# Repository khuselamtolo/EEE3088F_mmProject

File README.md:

# EEE3088F_mmProject
## PCB Designs of a power subsystem, intended for a micro-mouse maze-solving robot
This repository is for Group 64's design files for the Micro-mouse Power Subsystem Project, as required by the EEE3088F course from the University of Cape Town.

We, as the students, give our consent for third parties to use, modify, distribute and sell the files found within in repository, but please contact the University of Cape Town for full legal licensing.

Group 64's Student Numbers: MTLKHU009, VRSNEO001

## Repository File Layout
In the main directory of the repository (where this README.md file is) is the main files of the project (.kicad_pro .kicad_sch and .kicad_pcb).
The folder 'jlcpcb' contains the production files, formatted for the manufacturer JLCPCB.
The folders 'Connector_USB.lib' and 'Connector_USB.pretty' contain footprint files for USB connectors, for either Windows or MacOS (respectively). These files are referenced for the USB-C connector in the project.

## How to use
Download the repository, and open the file 'EEE3088F_micro_mouse_power_subsystem.kicad_pro' using Ki_CAD 9.0 or any later version that's compatible with KiCAD 9.0 files.

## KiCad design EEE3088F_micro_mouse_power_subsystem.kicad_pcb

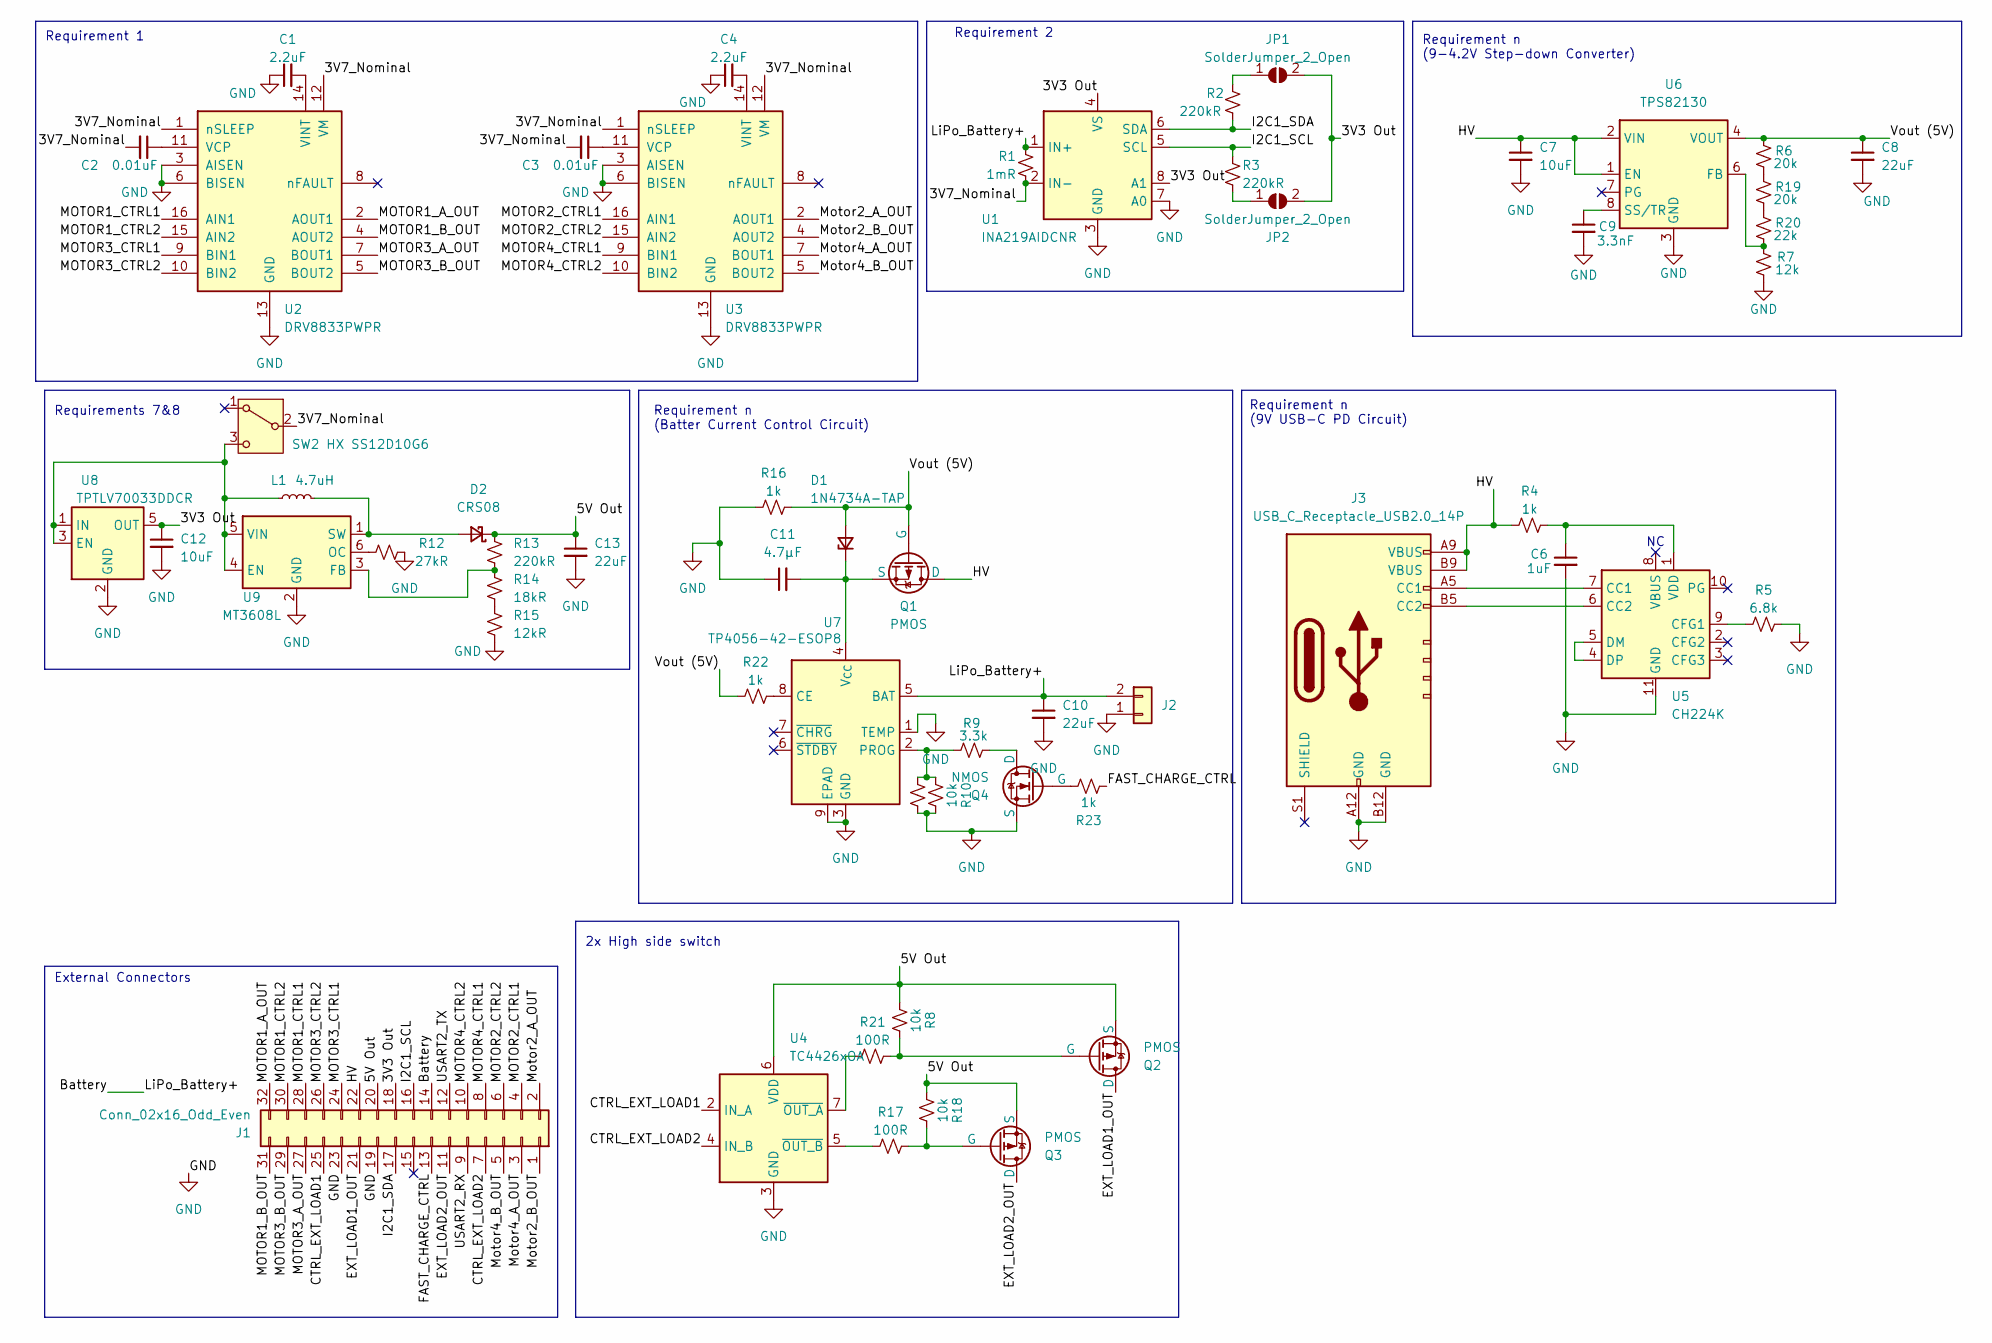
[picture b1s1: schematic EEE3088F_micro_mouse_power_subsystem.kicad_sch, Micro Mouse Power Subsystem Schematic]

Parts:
C1, C4: 2.2uF; C_0402_1005Metric; LCSC C12530
C2, C3: 0.01uF; C_0402_1005Metric; LCSC C15195
C6: 1uF; C_0402_1005Metric; LCSC C1848
C7, C12: 10uF; C_0402_1005Metric; LCSC C15525
C8, C10, C13: 22uF; C_0603_1608Metric; LCSC C59461
C9: 3.3nF; C_0603_1608Metric; LCSC C1613
C11: 4.7µF; C_0805_2012Metric; LCSC C1779
D1: 1N4734A-TAP; D_DO-35_SOD27_P2.54mm_Vertical_AnodeUp; LCSC C241984
D2: CRS08; D_1206_3216Metric; LCSC C475662
J1: Conn_02x16_Odd_Even; PinHeader_2x16_P2.54mm_Vertical
J2: Conn_01x02; JST_PH_S2B-PH-K_1x02_P2.00mm_Horizontal
J3: USB_C_Receptacle_USB2.0_14P; USB_C_Receptacle_GCT_USB4125-xx-x-0190_6P_TopMnt_Horizontal; LCSC C168701
JP1, JP2: SolderJumper_2_Open; SolderJumper-2_P1.3mm_Open_TrianglePad1.0x1.5mm
L1: 4.7uH; L_1008_2520Metric; LCSC C5832360
Q1, Q2, Q3: PMOS; SOT-23; LCSC C5224173
Q4: NMOS; SOT-23; LCSC C8545
R1: 1mR; R_1206_3216Metric; LCSC C7419993
R2, R3, R13: 220kR; R_0603_1608Metric; LCSC C22961
R4, R16, R22, R23: 1k; R_1206_3216Metric; LCSC C4410
R5: 6.8k; R_0805_2012Metric; LCSC C17772
R6, R19: 20k; R_0603_1608Metric; LCSC C4184
R7: 12k; R_0402_1005Metric; LCSC C25752
R8, R10, R11, R18: 10k; R_0603_1608Metric; LCSC C25804
R9: 3.3k; R_0603_1608Metric; LCSC C22978
R12: 27kR; R_0603_1608Metric; LCSC C22967
R14: 18kR; R_0603_1608Metric; LCSC C25810
R15: 12kR; R_0402_1005Metric; LCSC C25752
R17, R21: 100R; R_0805_2012Metric; LCSC C17408
R20: 22k; R_0603_1608Metric; LCSC C31850
SW2: HX SS12D10G6; SolderWire-0.75sqmm_1x03_P4.8mm_D1.25mm_OD2.3mm; LCSC C19189121
U1: INA219AIDCNR; SOT-23-8; LCSC C87469
U2, U3: DRV8833PWPR; TSSOP-16_4.4x5mm_P0.65mm; LCSC C50506
U4: TC4426xOA; SOIC-8_3.9x4.9mm_P1.27mm
U5: CH224K; SSOP-10-1EP_3.9x4.9mm_P1mm_EP2.1x3.3mm; LCSC C970725
U6: TPS82130; Texas_SIL0008D_MicroSiP-8-1EP_2.8x3mm_P0.65mm_EP1.1x1.9mm_T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; LCSC C473914
U7: TP4056-42-ESOP8; SOIC-8-1EP_3.9x4.9mm_P1.27mm_EP2.41x3.3mm_ThermalVias; LCSC C21417
U8: TPTLV70033DDCR; SOT-23-5; LCSC C2937039
U9: MT3608L; SOT-23-6; LCSC C2932326

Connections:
/3V3 Out: C12.1, J1.18, JP1.2 (B), JP2.2 (B), U1.4 (VS), U1.8 (A1), U8.5 (OUT)
/3V7_Nominal: C2.2, C3.2, R1.2, SW2.2 (B), U1.2 (IN-), U2.1 (nSLEEP), U2.12 (VM), U3.1 (nSLEEP), U3.12 (VM)
/5V Out: C13.1, D2.1 (K), J1.20, Q2.3 (S), Q3.3 (S), R8.1, R13.1, R18.1, U4.6 (VDD)
/Battery: C10.1, J1.14, J2.2 (Pin_1), R1.1, U1.1 (IN+), U7.5 (BAT)
/CTRL_EXT_LOAD1: J1.25, U4.2 (IN_A)
/CTRL_EXT_LOAD2: J1.7, U4.4 (IN_B)
/EXT_LOAD1_OUT: J1.21, Q2.1 (D)
/EXT_LOAD2_OUT: J1.11, Q3.1 (D)
/FAST_CHARGE_CTRL: J1.13, R23.2
/HV: C7.1, J1.22, J3.A9 (VBUS), J3.B4 (VBUS), J3.B9 (VBUS), Q1.1 (D), R4.2, U6.1 (EN), U6.2 (VIN)
/I2C1_SCL: J1.16, R3.1, U1.5 (SCL)
/I2C1_SDA: J1.17, R2.2, U1.6 (SDA)
/MOTOR1_A_OUT: J1.32, U2.2 (AOUT1)
/MOTOR1_B_OUT: J1.31, U2.4 (AOUT2)
/MOTOR1_CTRL1: J1.28, U2.16 (AIN1)
/MOTOR1_CTRL2: J1.30, U2.15 (AIN2)
/MOTOR2_CTRL1: J1.4, U3.16 (AIN1)
/MOTOR2_CTRL2: J1.6, U3.15 (AIN2)
/MOTOR3_A_OUT: J1.27, U2.7 (BOUT1)
/MOTOR3_B_OUT: J1.29, U2.5 (BOUT2)
/MOTOR3_CTRL1: J1.24, U2.9 (BIN1)
/MOTOR3_CTRL2: J1.26, U2.10 (BIN2)
/MOTOR4_CTRL1: J1.8, U3.9 (BIN1)
/MOTOR4_CTRL2: J1.10, U3.10 (BIN2)
/Motor2_A_OUT: J1.2, U3.2 (AOUT1)
/Motor2_B_OUT: J1.1, U3.4 (AOUT2)
/Motor4_A_OUT: J1.3, U3.7 (BOUT1)
/Motor4_B_OUT: J1.5, U3.5 (BOUT2)
/USART2_RX: J1.9
/USART2_TX: J1.12
/Vout (5V): C8.1, D1.2 (A), Q1.2 (G), R6.1, R16.1, R22.2, U6.4 (VOUT), U6.5 (VOUT)
GND: C1.1, C4.1, C6.2, C7.2, C8.2, C9.2, C10.2, C11.1, C12.2, C13.2, J1.19, J1.23, J2.1 (Pin_2), J3.A12 (GND), J3.B1 (GND), J3.B12 (GND), Q4.3 (S), R5.2, R7.2, R10.2, R11.2, R12.2, R15.2, R16.2, U1.3 (GND), U1.7 (A0), U2.3 (AISEN), U2.6 (BISEN), U2.13 (GND), U3.3 (AISEN), U3.6 (BISEN), U3.13 (GND), U4.3 (GND), U5.11 (GND), U6.3 (GND), U6.9 (GND), U7.1 (TEMP), U7.3 (GND), U7.9 (EPAD), U8.2 (GND), U8.4 (GND), U9.2 (GND)
unnamed: C11.2, D1.1 (K), Q1.3 (S), U7.4 (V_{CC})
unnamed: D2.2 (A), L1.2, U9.1 (SW)
unnamed: J3.A5 (CC1), U5.7 (CC1)
unnamed: J3.B5 (CC2), U5.6 (CC2)
unnamed: JP1.1 (A), R2.1
unnamed: JP2.1 (A), R3.2
unnamed: Q2.2 (G), R8.2, R21.2
unnamed: Q3.2 (G), R17.2, R18.2
unnamed: Q4.1 (D), R9.2
unnamed: Q4.2 (G), R23.1
unnamed: R14.2, R15.1
unnamed: R6.2, R19.1
unnamed: R19.2, R20.1
unnamed: L1.1, SW2.3 (C), U8.1 (IN), U8.3 (EN), U9.4 (EN), U9.5 (VIN)
unnamed: C2.1, U2.11 (VCP)
unnamed: C1.2, U2.14 (VINT)
unnamed: C3.1, U3.11 (VCP)
unnamed: C4.2, U3.14 (VINT)
unnamed: R21.1, U4.7 (~OUT_A)
unnamed: R17.1, U4.5 (~OUT_B)
unnamed: R5.1, U5.9 (CFG1)
unnamed: U5.4 (DP), U5.5 (DM)
unnamed: C6.1, R4.1, U5.1 (VDD)
unnamed: R7.1, R20.2, U6.6 (FB)
unnamed: C9.1, U6.8 (SS/TR)
unnamed: R22.1, U7.8 (CE)
unnamed: R9.1, R10.1, R11.1, U7.2 (PROG)
unnamed: R13.2, R14.1, U9.3 (FB)
unnamed: R12.1, U9.6 (OC)

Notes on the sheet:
Requirement n (9-4.2V Step-down Converter)
Requirement n (9V USB-C PD Circuit)
2x High side switch
Requirement 1
Requirement n (Batter Current Control Circuit)
Requirements 7&8
External Connectors
Requirement 2

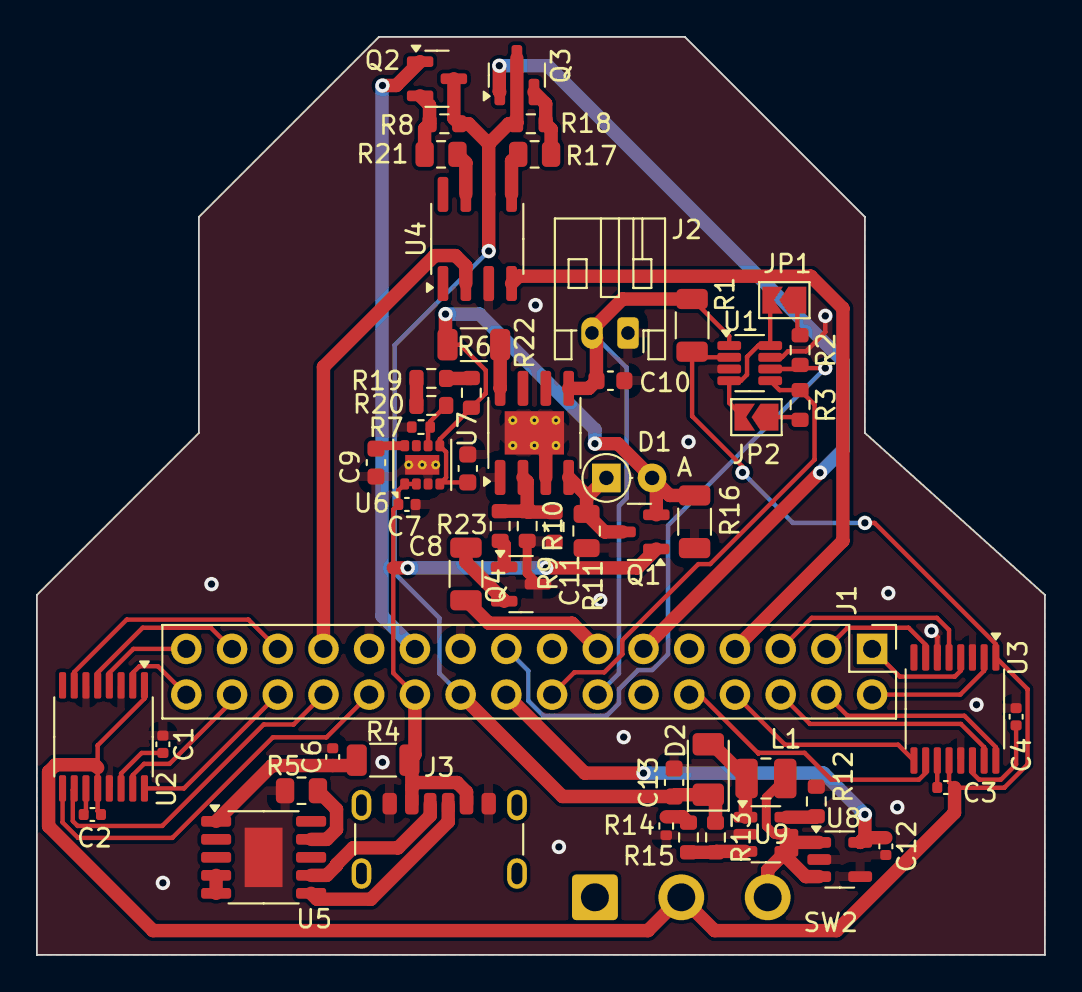
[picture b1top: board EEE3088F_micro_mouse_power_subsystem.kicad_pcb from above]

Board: 2 copper layers, 56.0 x 51.0 mm, 57 parts (0 on the bottom side), 59 nets.

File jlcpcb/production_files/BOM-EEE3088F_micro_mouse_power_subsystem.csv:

Comment,Designator,Footprint,LCSC,Quantity
2.2uF,"C1,C4",C_0402_1005Metric,C12530,2
TC4426xOA,U4,SOIC-8_3.9x4.9mm_P1.27mm,C148047,1
0.01uF,"C2,C3",C_0402_1005Metric,C15195,2
10uF,"C12,C7",C_0402_1005Metric,C15525,2
3.3nF,C9,C_0603_1608Metric,C1613,1
100R,"R17,R21",R_0805_2012Metric,C17408,2
6.8k,R5,R_0805_2012Metric,C17772,1
4.7µF,C11,C_0805_2012Metric,C1779,1
1uF,C6,C_0402_1005Metric,C1848,1
HX SS12D10G6,SW2,SolderWire-0.75sqmm_1x03_P4.8mm_D1.25mm_OD2.3mm,C19189121,1
TP4056-42-ESOP8,U7,SOIC-8-1EP_3.9x4.9mm_P1.27mm_EP2.41x3.3mm_ThermalVias,C21417,1
220kR,"R13,R2,R3",R_0603_1608Metric,C22961,3
27kR,R12,R_0603_1608Metric,C22967,1
3.3k,R9,R_0603_1608Metric,C22978,1
1N4734A-TAP,D1,D_DO-35_SOD27_P2.54mm_Vertical_AnodeUp,C241984,1
12kR,"R15,R7",R_0402_1005Metric,C25752,2
10k,"R10,R11,R18,R8",R_0603_1608Metric,C25804,4
18kR,R14,R_0603_1608Metric,C25810,1
MT3608L,U9,SOT-23-6,C2932326,1
TPTLV70033DDCR,U8,SOT-23-5,C2937039,1
USB_C_Receptacle_USB2.0_14P,J3,USB_C_Receptacle_GCT_USB4125-xx-x-0190_6P_TopMnt_Horizontal,C3151746,1
22k,R20,R_0603_1608Metric,C31850,1
20k,"R19,R6",R_0603_1608Metric,C4184,2
1k,"R16,R22,R23,R4",R_1206_3216Metric,C4410,4
TPS82130,U6,Texas_SIL0008D_MicroSiP-8-1EP_2.8x3mm_P0.65mm_EP1.1x1.9mm_ThermalVias,C473914,1
CRS08,D2,D_1206_3216Metric,C475662,1
DRV8833PWPR,"U2,U3",TSSOP-16_4.4x5mm_P0.65mm,C50506,2
PMOS,"Q1,Q2,Q3",SOT-23,C5224173,3
4.7uH,L1,L_1008_2520Metric,C5832360,1
22uF,"C10,C13,C8",C_0603_1608Metric,C59461,3
1mR,R1,R_1206_3216Metric,C7419993,1
NMOS,Q4,SOT-23,C8545,1
INA219AIDCNR,U1,SOT-23-8,C87469,1
CH224K,U5,SSOP-10-1EP_3.9x4.9mm_P1mm_EP2.1x3.3mm,C970725,1

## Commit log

2025-03-24 Added a legal notice to the README file
2025-03-24 Added KiCad project with 02x16 pins
2025-03-25 Added circuit for Requirement 2
2025-03-25 Added circuit for Requirement 1
2025-03-25 test commit
    Just testing
2025-03-25 Updated LCSC numbers and Requirements 7 and 8
2025-03-25 Battery charging circuitry added
2025-03-25 Added circuits for requirements 7 and 8
2025-03-26 Minor updates after meeting
2025-03-27 Added footprints for half of the components
2025-03-27 Final changes to schematic and footprints
2025-03-28 Created PCB layout and production files
2025-05-15 Deleted unnecessary files, like the back up files and cache
